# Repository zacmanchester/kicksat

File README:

kicksat
=======

## This repository is no longer being updated.
## All KickSat-related work is now hosted at [github.com/kicksat](https://github.com/kicksat)

# License

[Creative Commons Attribution-ShareAlike 4.0 International](https://creativecommons.org/licenses/by-sa/4.0/)

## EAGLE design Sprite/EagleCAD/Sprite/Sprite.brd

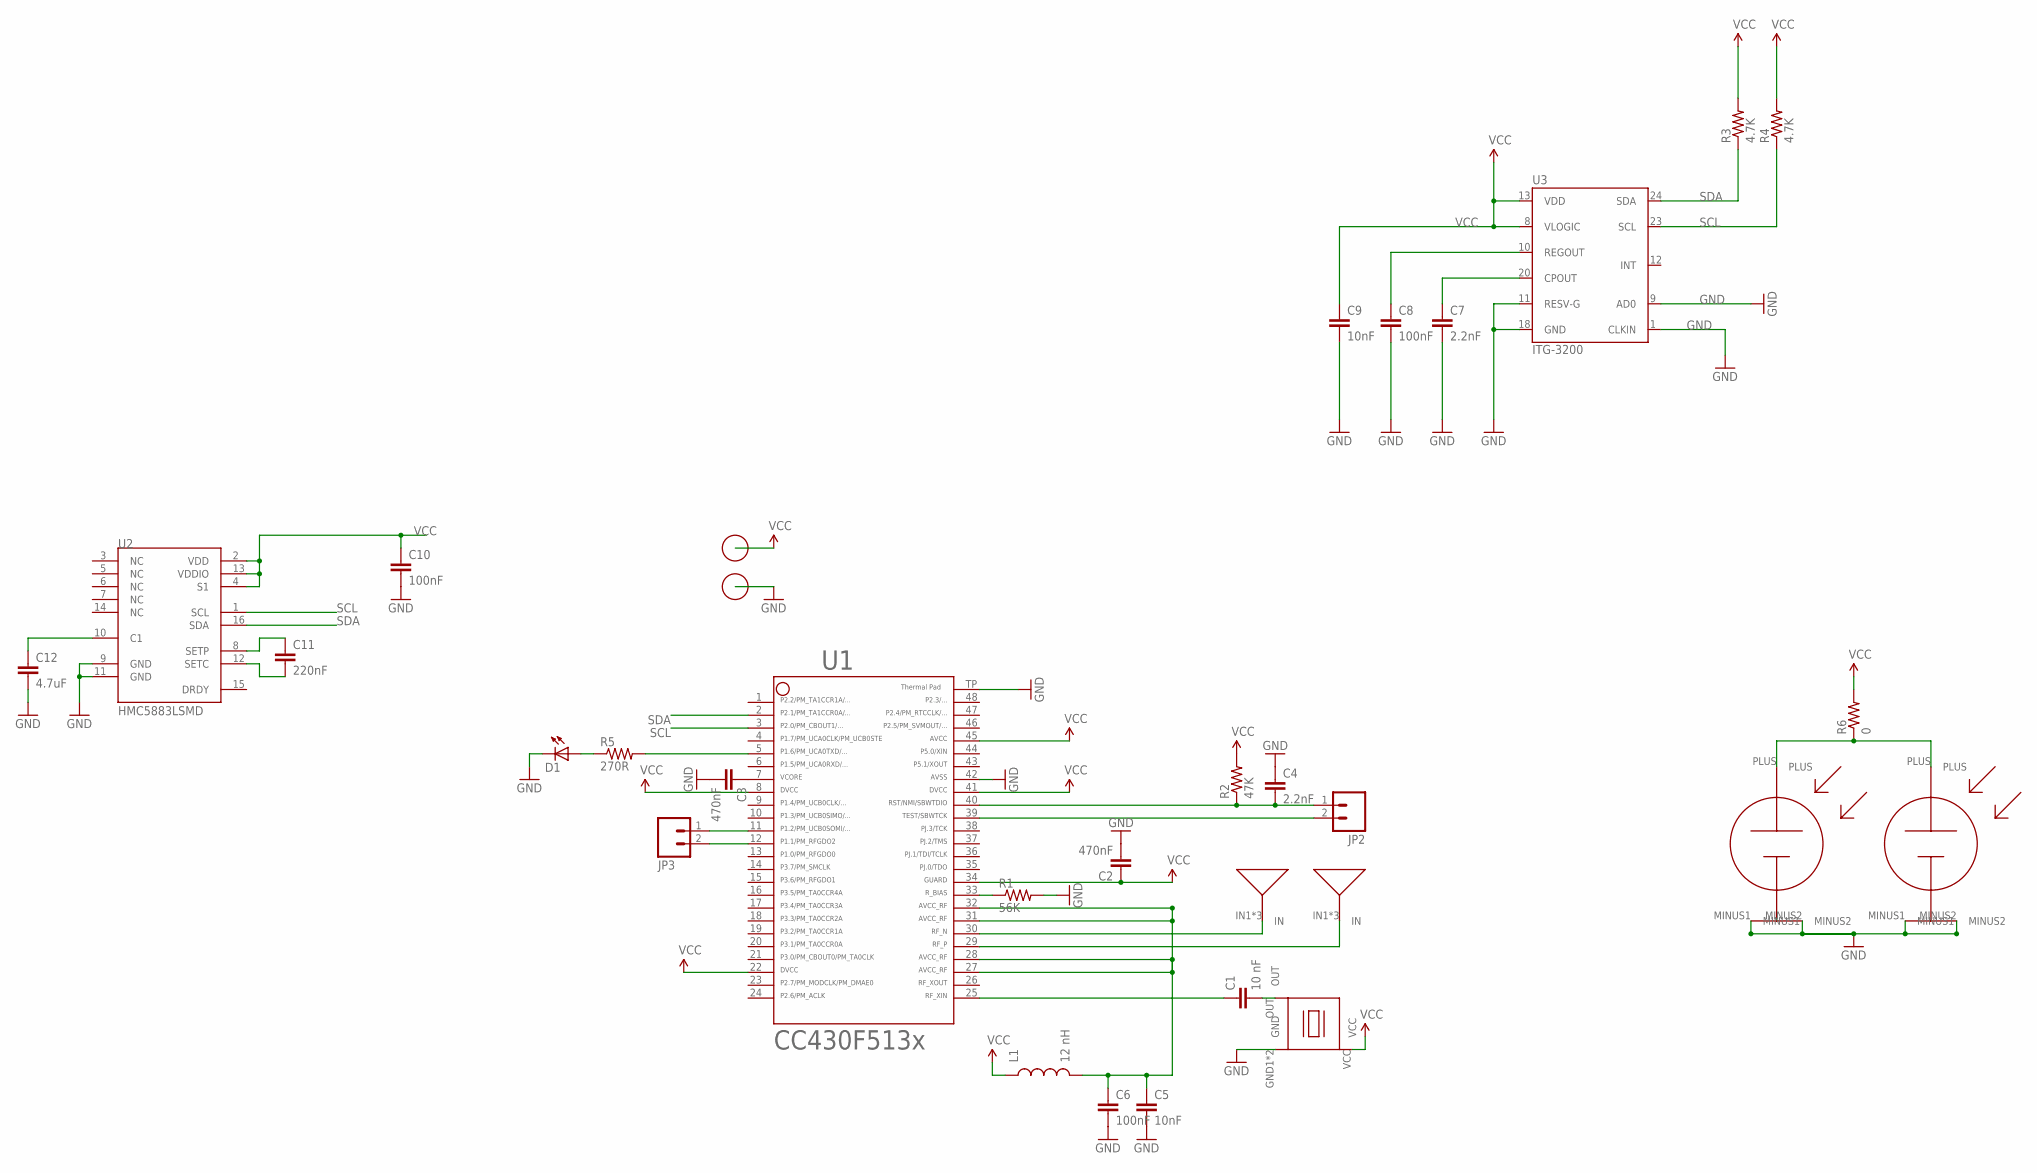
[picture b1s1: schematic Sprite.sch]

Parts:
ANT-N: ANTENNA
ANT-P: ANTENNA
C1: 10 nF; 0603-CAP
C2, C3: 470nF; 0603-CAP
C4, C7: 2.2nF; 0603-CAP
C5, C9: 10nF; 0603-CAP
C6, C8, C10: 100nF; 0603-CAP
C11: 220nF; 0603-CAP
C12: 4.7uF; 0603-CAP
D1: LED0603; LED-0603
JP2, JP3: M02PTH; 1X02
L1: 12 nH; 0603
P1, P2: SPRITE_PIN
R1: 56K; 0603-RES
R2: 47K; 0603-RES
R3, R4: 4.7K; 0603-RES
R5: 270R; 0603-RES
R6: 0; R0805
S1, S2: TASC
U1: CC430F5137; RGZ48
U2: HMC5883LSMD; 16LPCC
U3: ITG-3200; QFN-24
X1: TCXO_7Z; TXC_7Z

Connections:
GND: C2.2, C3.2, C4.1, C5.2, C6.2, C7.2, C8.2, C9.2, C10.2, C12.2, D1.C, R1.2, S1.MINUS1, S1.MINUS2, S2.MINUS1, S2.MINUS2, U1.42, U1.TP (49), U2.9 (GND), U2.11 (GND), U3.1 (CLKIN), U3.9 (AD0), U3.11 (RESV-G), U3.18 (GND), X1.GND1 (GND), X1.GND2 (GND)
unnamed: C1.1, U1.25
unnamed: R1.1, U1.33
unnamed: C3.1, U1.7
unnamed: C11.1, U2.8 (SETP)
unnamed: C11.2, U2.12 (SETC)
unnamed: C12.1, U2.10 (C1)
unnamed: C7.1, U3.20 (CPOUT)
unnamed: C8.1, U3.10 (REGOUT)
unnamed: R5.2, U1.5
unnamed: D1.A, R5.1
unnamed: C1.2, X1.OUT
RFN: ANT-N.IN1, ANT-N.IN2, ANT-N.IN3, U1.30
RFP: ANT-P.IN1, ANT-P.IN2, ANT-P.IN3, U1.29
RST: C4.2, JP2.1, R2.1, U1.40
RXD: JP3.2, U1.12
SCL: R4.1, U1.3, U2.1 (SCL), U3.23 (SCL)
SDA: R3.1, U1.2, U2.16 (SDA), U3.24 (SDA)
TEST: JP2.2, U1.39
TXD: JP3.1, U1.11
VCC: C2.1, C9.1, C10.1, L1.1, R2.2, R3.2, R4.2, R6.2, U1.8, U1.22, U1.34, U1.41, U1.45, U2.2 (VDD), U2.4 (S1), U2.13 (VDDIO), U3.8 (VLOGIC), U3.13 (VDD), X1.VCC
VCCRF: C5.1, C6.1, L1.2, U1.27, U1.28, U1.31, U1.32
VSOLAR: R6.1, S1.PLUS, S2.PLUS

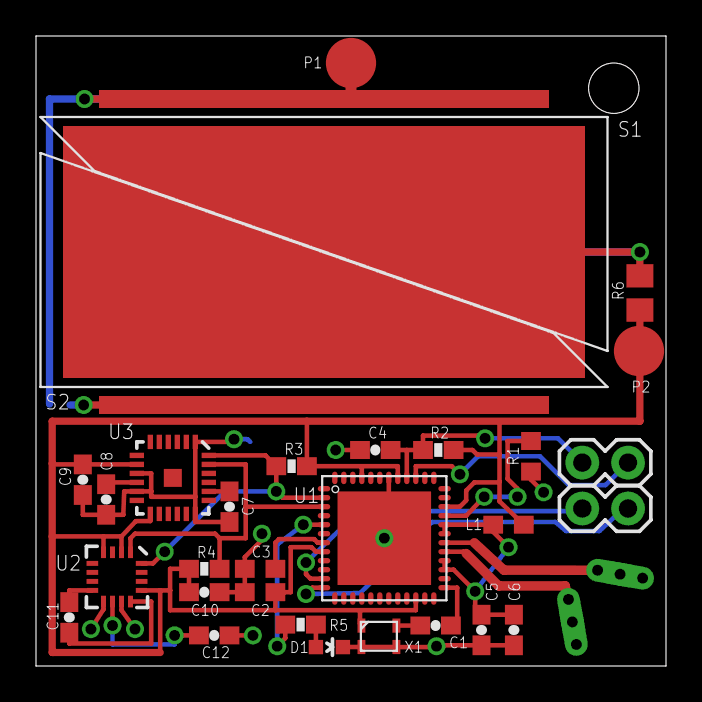
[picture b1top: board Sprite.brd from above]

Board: 2 copper layers, 35.0 x 35.0 mm, 32 parts (1 on the bottom side), 23 nets.

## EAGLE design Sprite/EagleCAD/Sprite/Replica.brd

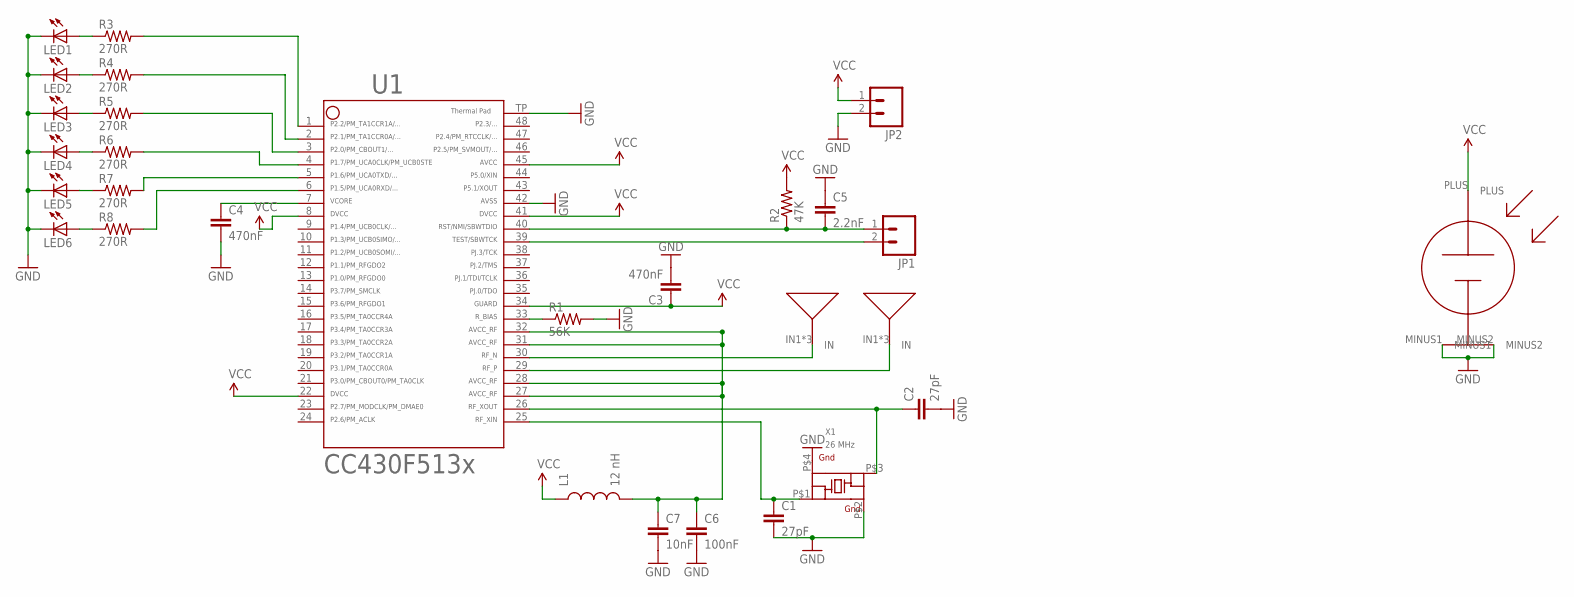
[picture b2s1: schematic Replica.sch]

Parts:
ANT-N: ANTENNA
ANT-P: ANTENNA
C1, C2: 27pF; 0603-CAP
C3, C4: 470nF; 0603-CAP
C5: 2.2nF; 0603-CAP
C6: 100nF; 0603-CAP
C7: 10nF; 0603-CAP
JP1, JP2: M02PTH; 1X02
L1: 12 nH; 0603
LED1, LED2, LED3, LED4, LED5, LED6: LED0603; LED-0603
R1: 56K; 0603-RES
R2: 47K; 0603-RES
R3, R4, R5, R6, R7, R8: 270R; 0603-RES
S1: TASC
U1: CC430F5137; RGZ48
X1: 26 MHz; ABM11_CERAMIC-SMD-CRYSTAL

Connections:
GND: C1.2, C2.2, C3.2, C4.2, C5.1, C6.2, C7.2, JP2.2, LED1.C, LED2.C, LED3.C, LED4.C, LED5.C, LED6.C, R1.2, S1.MINUS1, S1.MINUS2, U1.42, U1.TP (49), X1.P$2 (GROUND2), X1.P$4 (GROUND4)
unnamed: C2.1, U1.26, X1.P$3
unnamed: C1.1, U1.25, X1.P$1
unnamed: R1.1, U1.33
unnamed: R4.2, U1.2
unnamed: LED2.A, R4.1
unnamed: LED3.A, R5.1
unnamed: LED4.A, R6.1
unnamed: LED5.A, R7.1
unnamed: LED6.A, R8.1
unnamed: R3.2, U1.1
unnamed: LED1.A, R3.1
unnamed: R5.2, U1.3
unnamed: R6.2, U1.4
unnamed: R7.2, U1.5
unnamed: R8.2, U1.6
RFN: ANT-N.IN1, ANT-N.IN2, ANT-N.IN3, U1.30
RFP: ANT-P.IN1, ANT-P.IN2, ANT-P.IN3, U1.29
RST: C5.2, JP1.1, R2.1, U1.40
TEST: JP1.2, U1.39
VCC: C3.1, JP2.1, L1.1, R2.2, S1.PLUS, U1.8, U1.22, U1.34, U1.41, U1.45
VCCRF: C6.1, C7.1, L1.2, U1.27, U1.28, U1.31, U1.32
VCORE: C4.1, U1.7

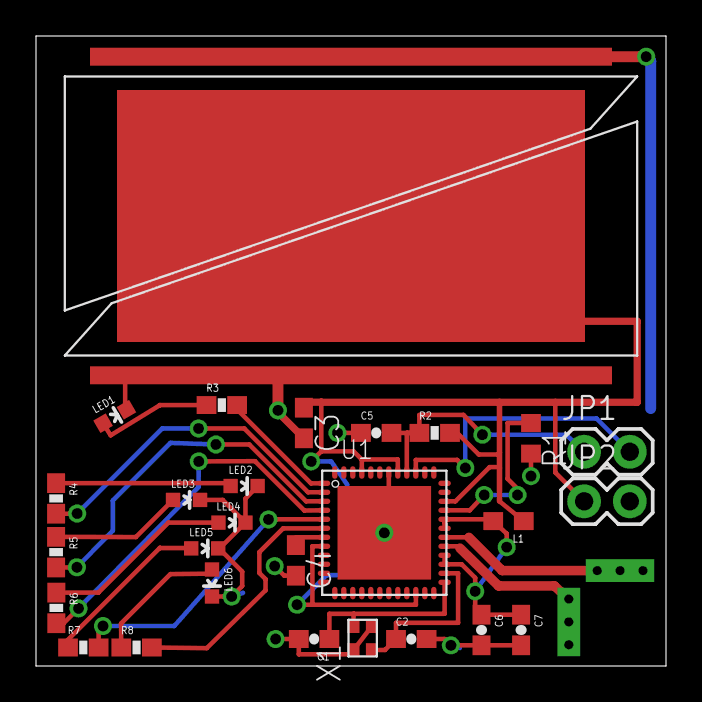
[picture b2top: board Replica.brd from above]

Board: 2 copper layers, 35.0 x 35.0 mm, 29 parts (0 on the bottom side), 23 nets.

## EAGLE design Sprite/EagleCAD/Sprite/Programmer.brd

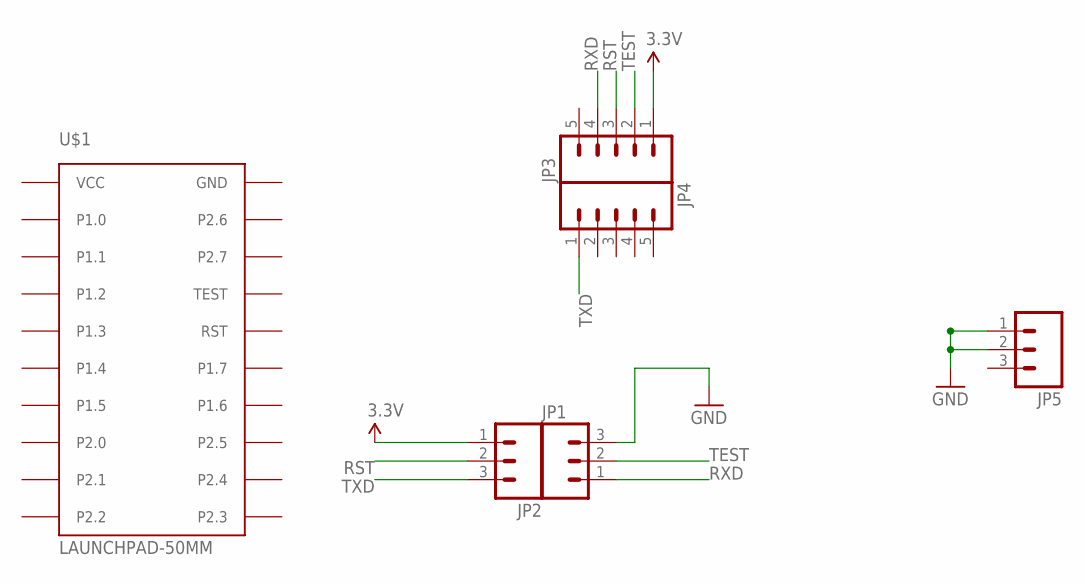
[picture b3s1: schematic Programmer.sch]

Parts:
JP1, JP2, JP5: M03LOCK; 1X03_LOCK
JP3, JP4: M05LOCK; 1X05_LOCK
U$1: LAUNCHPAD-50MM

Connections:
3.3V: JP2.1, JP3.1
GND: JP1.3, JP5.1, JP5.2, U$1.GND
RST: JP2.2, JP3.3
RXD: JP1.1, JP3.4
TEST: JP1.2, JP3.2
TXD: JP2.3, JP4.1
VCC: U$1.VCC

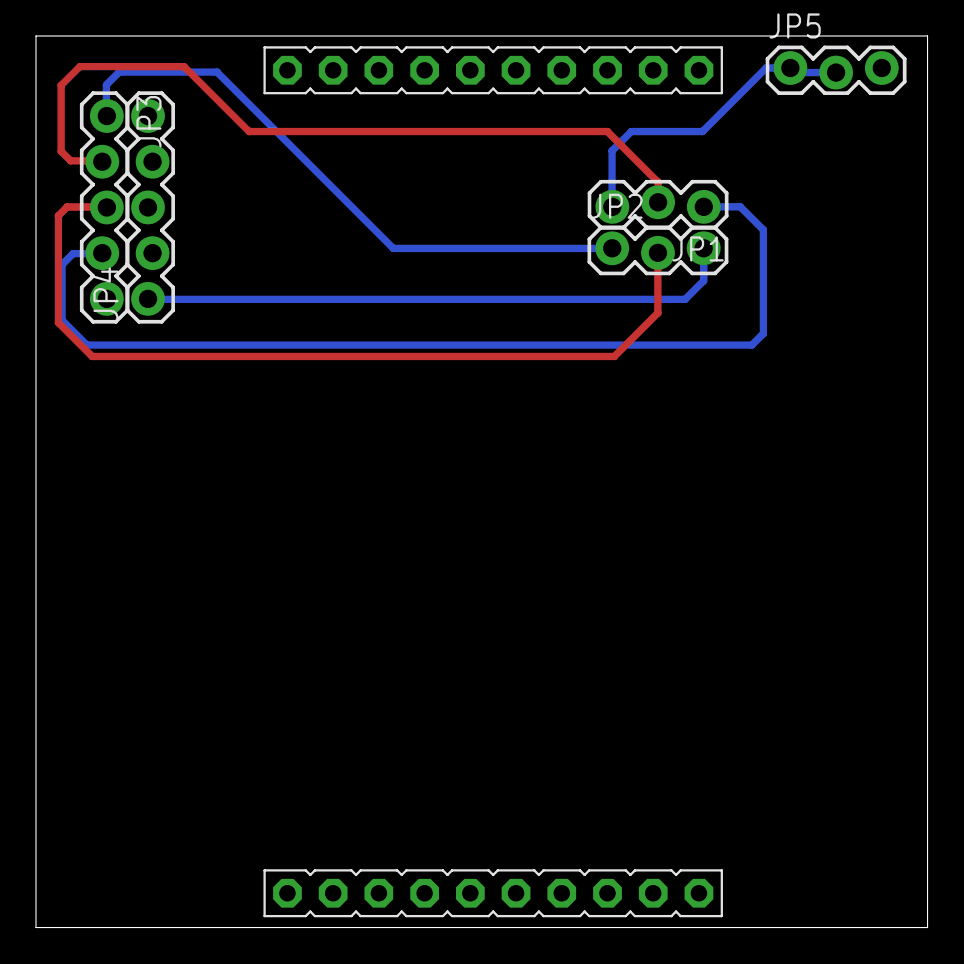
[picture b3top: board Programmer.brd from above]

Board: 2 copper layers, 49.5 x 49.5 mm, 6 parts (0 on the bottom side), 6 nets.

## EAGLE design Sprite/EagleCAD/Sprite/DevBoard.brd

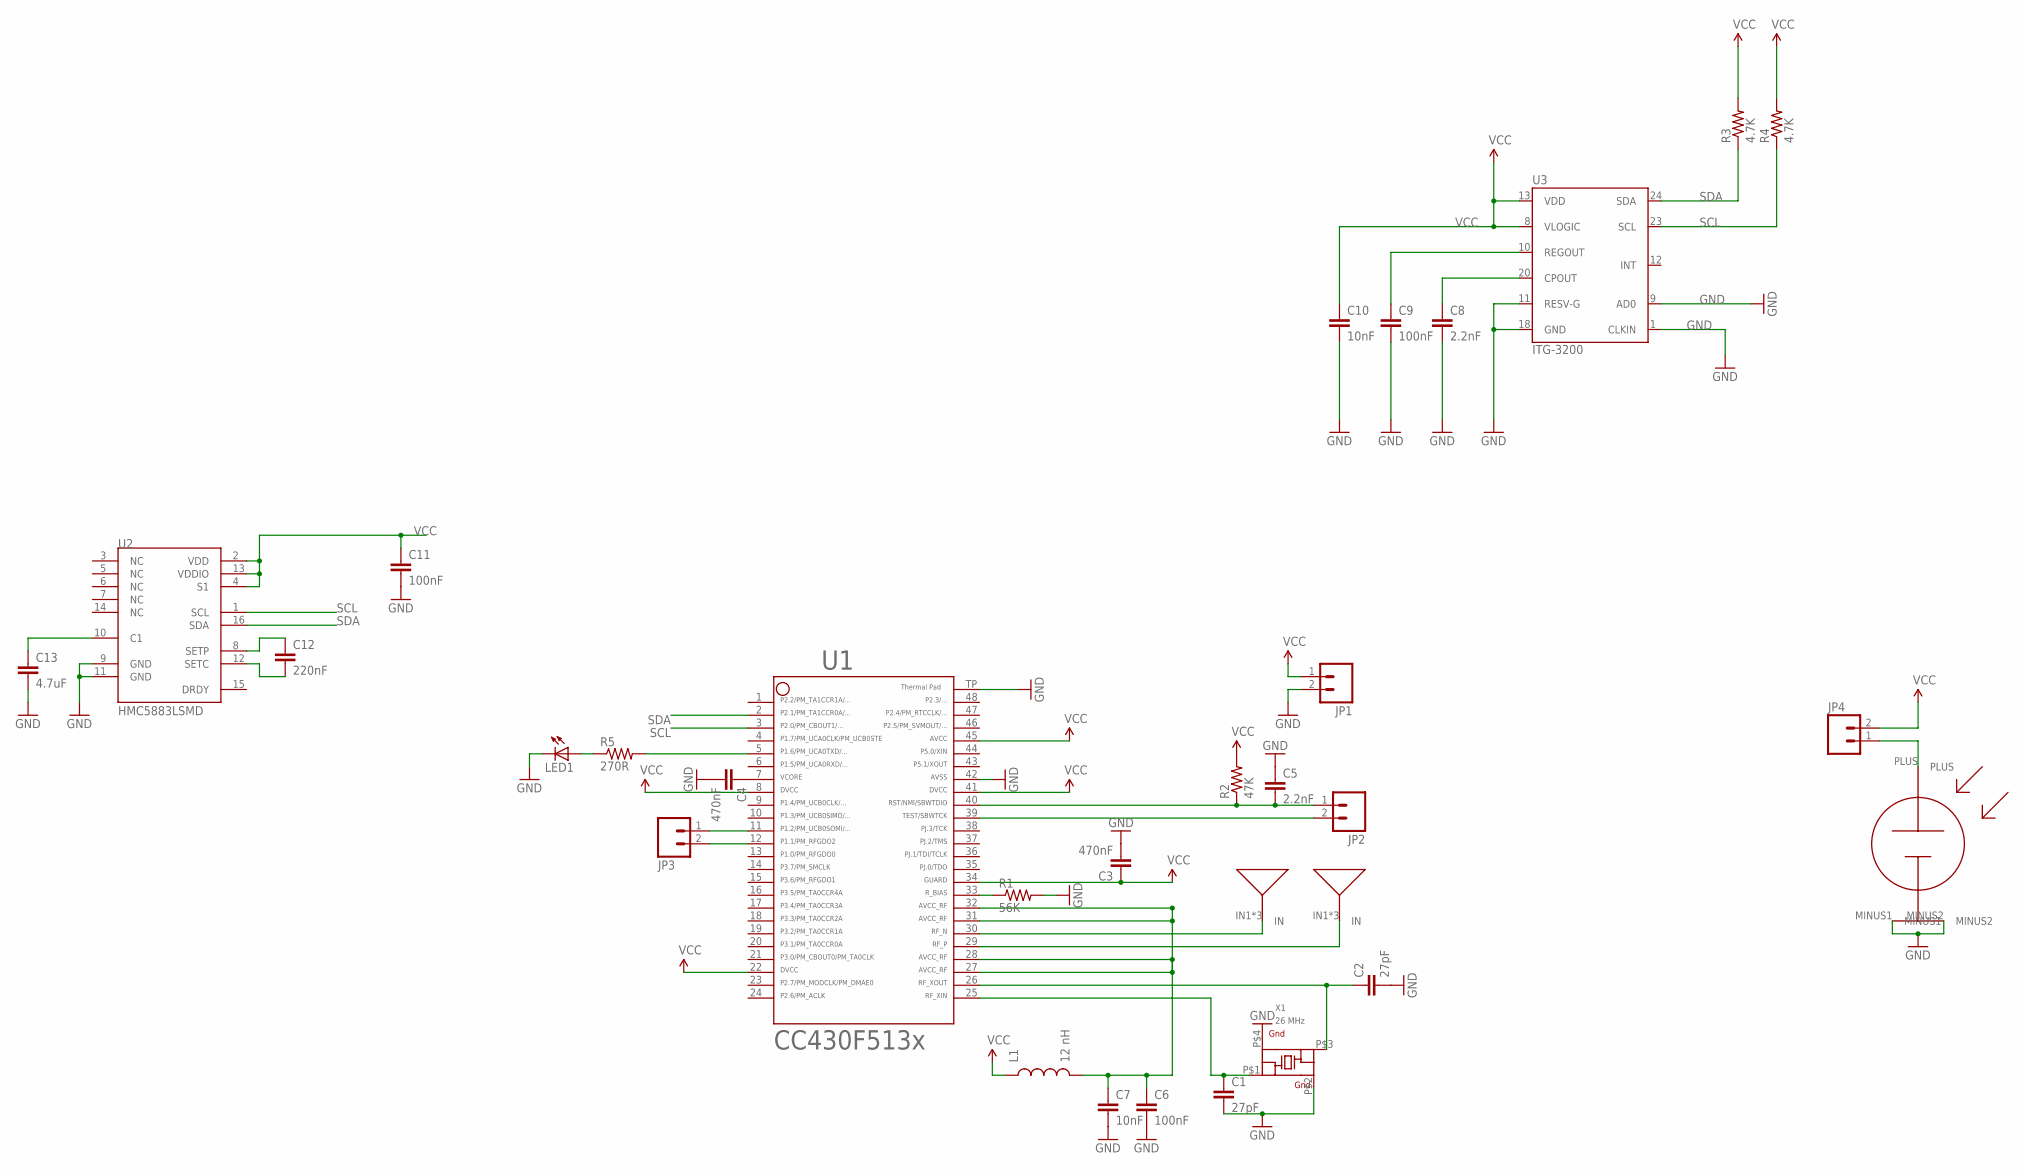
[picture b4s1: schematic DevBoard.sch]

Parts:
ANT-N: ANTENNA
ANT-P: ANTENNA
C1, C2: 27pF; 0603-CAP
C3, C4: 470nF; 0603-CAP
C5, C8: 2.2nF; 0603-CAP
C6, C9, C11: 100nF; 0603-CAP
C7, C10: 10nF; 0603-CAP
C12: 220nF; 0603-CAP
C13: 4.7uF; 0603-CAP
JP1, JP2, JP3, JP4: M02PTH; 1X02
L1: 12 nH; 0603
LED1: LED0603; LED-0603
R1: 56K; 0603-RES
R2: 47K; 0603-RES
R3, R4: 4.7K; 0603-RES
R5: 270R; 0603-RES
S1: TASC
U1: CC430F5137; RGZ48
U2: HMC5883LSMD; 16LPCC
U3: ITG-3200; QFN-24
X1: 26 MHz; ABM11_CERAMIC-SMD-CRYSTAL

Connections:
GND: C1.2, C2.2, C3.2, C4.2, C5.1, C6.2, C7.2, C8.2, C9.2, C10.2, C11.2, C13.2, JP1.2, LED1.C, R1.2, S1.MINUS1, S1.MINUS2, U1.42, U1.TP (49), U2.9 (GND), U2.11 (GND), U3.1 (CLKIN), U3.9 (AD0), U3.11 (RESV-G), U3.18 (GND), X1.P$2 (GROUND2), X1.P$4 (GROUND4)
unnamed: C2.1, U1.26, X1.P$3
unnamed: C1.1, U1.25, X1.P$1
unnamed: R1.1, U1.33
unnamed: C4.1, U1.7
unnamed: C12.1, U2.8 (SETP)
unnamed: C12.2, U2.12 (SETC)
unnamed: C13.1, U2.10 (C1)
unnamed: C8.1, U3.20 (CPOUT)
unnamed: C9.1, U3.10 (REGOUT)
unnamed: R5.2, U1.5
unnamed: LED1.A, R5.1
RFN: ANT-N.IN1, ANT-N.IN2, ANT-N.IN3, U1.30
RFP: ANT-P.IN1, ANT-P.IN2, ANT-P.IN3, U1.29
RST: C5.2, JP2.1, R2.1, U1.40
RX: JP3.1, U1.11
SCL: R4.1, U1.3, U2.1 (SCL), U3.23 (SCL)
SDA: R3.1, U1.2, U2.16 (SDA), U3.24 (SDA)
TEST: JP2.2, U1.39
TX: JP3.2, U1.12
VCC: C3.1, C10.1, C11.1, JP1.1, JP4.2, L1.1, R2.2, R3.2, R4.2, U1.8, U1.22, U1.34, U1.41, U1.45, U2.2 (VDD), U2.4 (S1), U2.13 (VDDIO), U3.8 (VLOGIC), U3.13 (VDD)
VCCRF: C6.1, C7.1, L1.2, U1.27, U1.28, U1.31, U1.32
VSOLAR: JP4.1, S1.PLUS

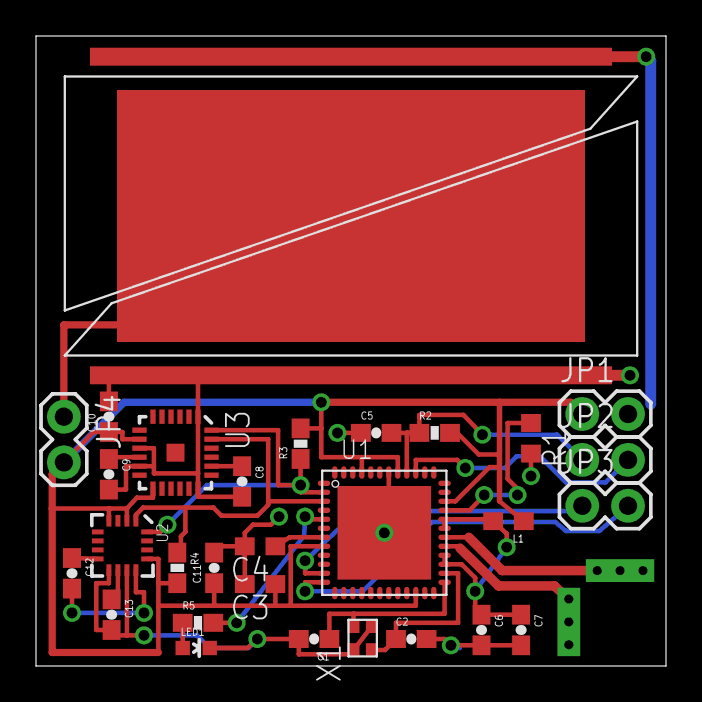
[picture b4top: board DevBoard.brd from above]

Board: 2 copper layers, 35.0 x 35.0 mm, 31 parts (0 on the bottom side), 23 nets.

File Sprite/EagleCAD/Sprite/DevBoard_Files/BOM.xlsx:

Part | Value | Device | Package
C1 | 27pF | CAP0603-CAP | 0603-CAP
C2 | 27pF | CAP0603-CAP | 0603-CAP
C3 | 470nF | CAP0603-CAP | 0603-CAP
C4 | 470nF | CAP0603-CAP | 0603-CAP
C5 | 2.2nF | CAP0603-CAP | 0603-CAP
C6 | 100nF | CAP0603-CAP | 0603-CAP
C7 | 10nF | CAP0603-CAP | 0603-CAP
C8 | 2.2nF | CAP0603-CAP | 0603-CAP
C9 | 100nF | CAP0603-CAP | 0603-CAP
C10 | 10nF | CAP0603-CAP | 0603-CAP
C11 | 100nF | CAP0603-CAP | 0603-CAP
C12 | 220nF | CAP0603-CAP | 0603-CAP
C13 | 4.7uF | CAP0603-CAP | 0603-CAP
JP1 | DNP | DNP | DNP
JP2 | DNP | DNP | DNP
JP3 | DNP | DNP | DNP
JP4 | DNP | DNP | DNP
L1 | 12nH | INDUCTOR | 0603-INDUCTOR
LED1 | LED0603 | LED-0603 | 0603-LED
R1 | 56K | RESISTOR0603-RES | 0603-RES
R2 | 47K | RESISTOR0603-RES | 0603-RES
R3 | 4.7K | RESISTOR0603-RES | 0603-RES
R4 | 4.7K | RESISTOR0603-RES | 0603-RES
R5 | 270R | RESISTOR0603-RES | 0603-RES
R6 | 0R | RESISTOR0805-RES | 0805-RES
R7 | 0R | RESISTOR0805-RES | 0805-RES
S1 | TASC | TASC | TASC
S2` | TASC | TASC | TASC
U1 | CC430F5137 | CC430F513X---RGZ48 | QFN-48
U2 | HMC5883LSMD | HMC5883LSMD | 16-LPCC
U3 | ITG-3200 | ITG-3200 | QFN-24
X1 | 26MHz | ABM11-XTAL | ABM11_CERAMIC_SMD_CRYSTALABM11

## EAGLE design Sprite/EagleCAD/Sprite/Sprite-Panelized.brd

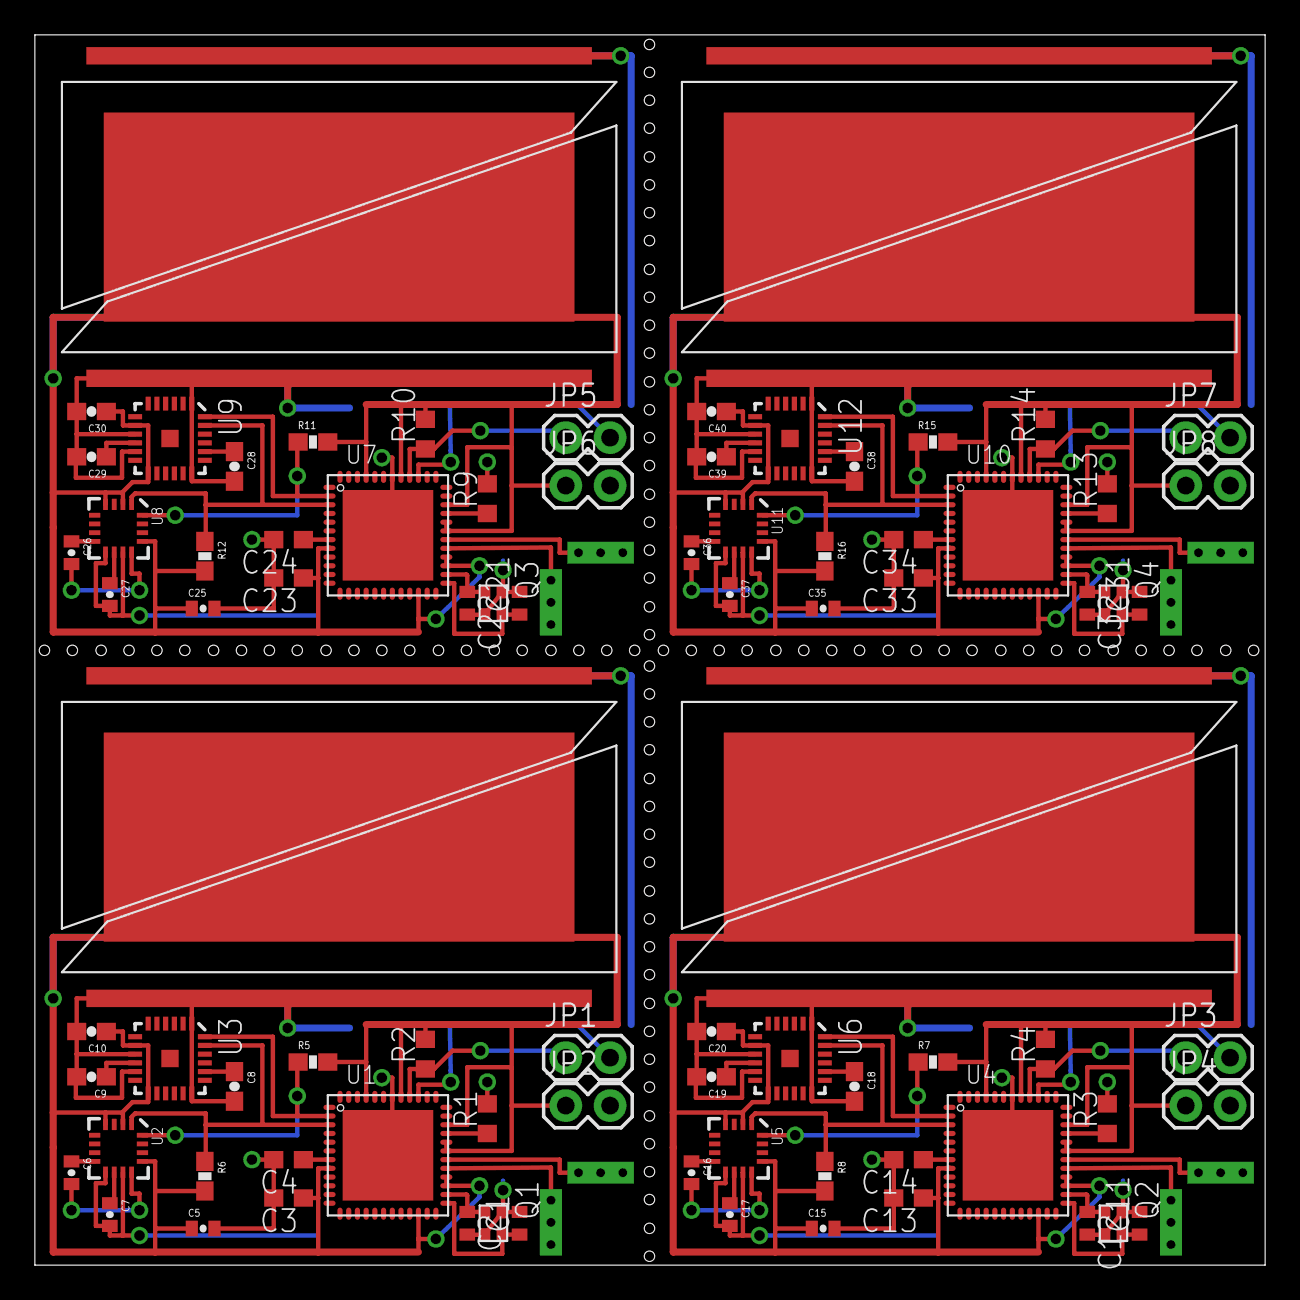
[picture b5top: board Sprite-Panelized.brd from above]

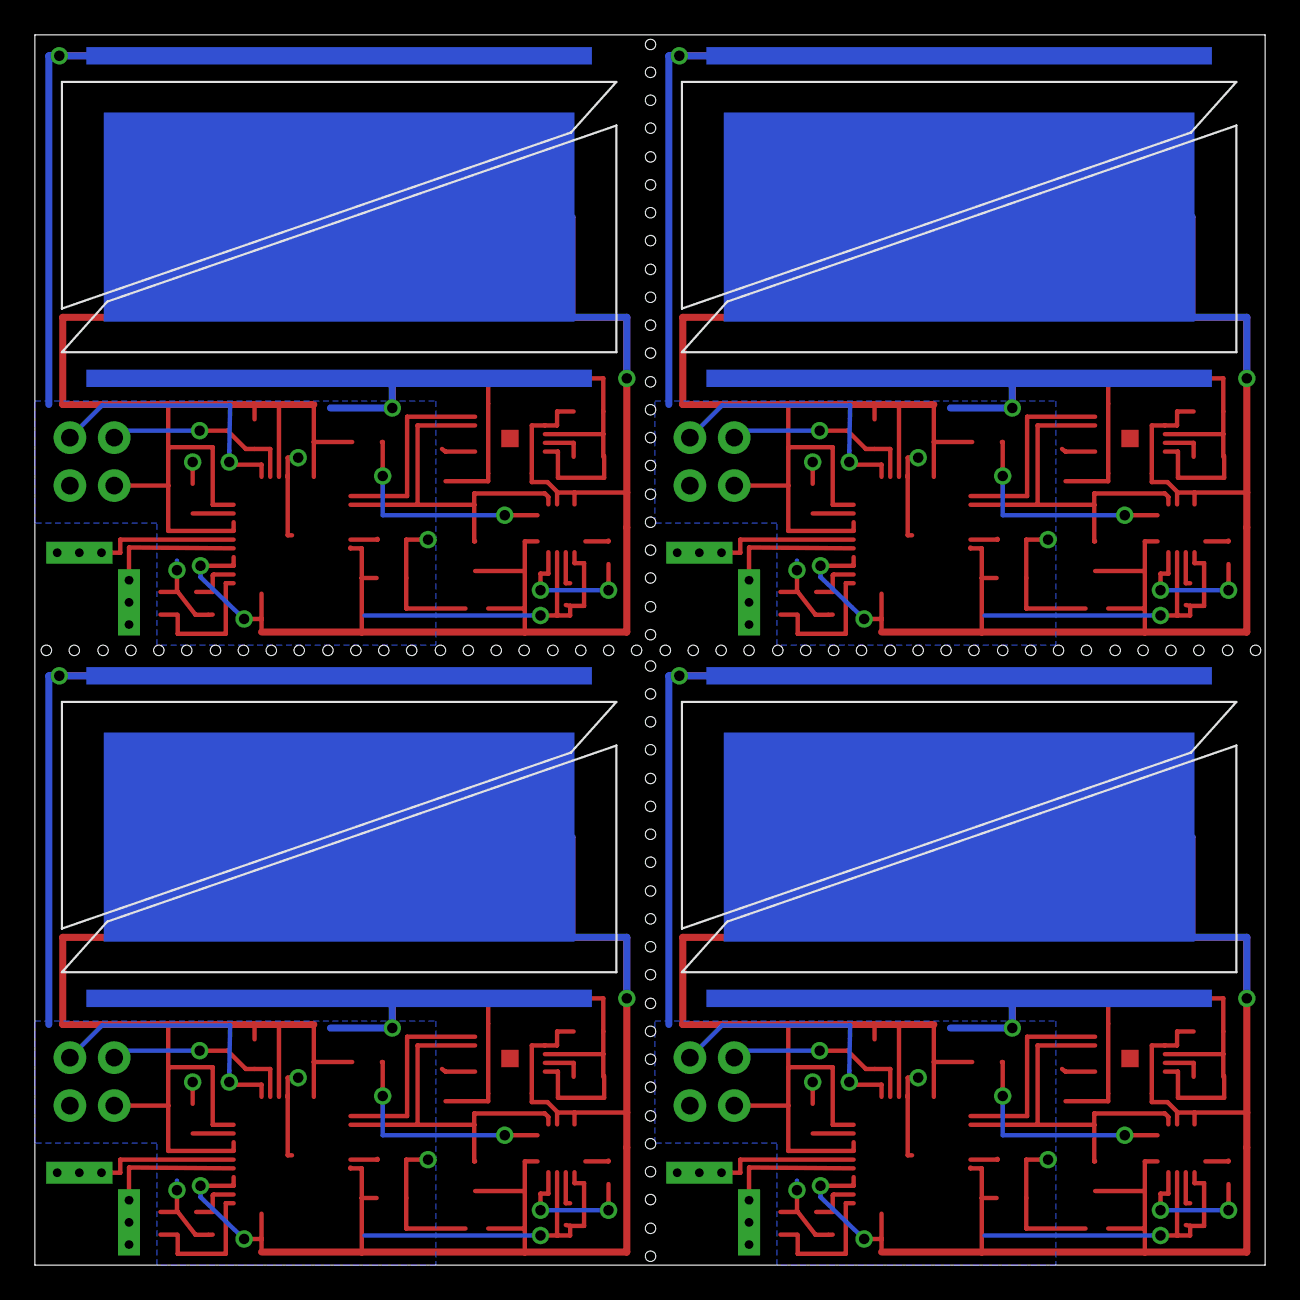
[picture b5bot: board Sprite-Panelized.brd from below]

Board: 2 copper layers, 70.6 x 70.6 mm, 96 parts (4 on the bottom side), 68 nets.

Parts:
C1, C2, C11, C12, C21, C22, C31, C32: 27 pF; C0402
C3, C4, C13, C14, C23, C24, C33, C34: 470 nF; C0603
C5, C15, C25, C35: .1uF; 0402-CAP
C6, C16, C26, C36: .22uF; 0402-CAP
C7, C17, C27, C37: 4.7uF; 0402-CAP
C8, C18, C28, C38: 2.2nF; 0603-CAP
C9, C19, C29, C39: 0.1uF; 0603-CAP
C10, C20, C30, C40: 10nF; 0603-CAP
JP1, JP2, JP3, JP4, JP5, JP6, JP7, JP8: 1X02
Q1, Q2, Q3, Q4: ABM11; ABM11_CERAMIC-SMD-CRYSTAL
R1, R3, R9, R13: 56 K; R0603
R2, R4, R10, R14: 47 K; R0603
R5, R6, R7, R8, R11, R12, R15, R16: DNP; 0603-RES
S1, S2, S3, S4, S5, S6, S7, S8: TASC
U1, U4, U7, U10: CC430F5137; RGZ48
U2, U5, U8, U11: HMC5883LSMD; 16LPCC
U3, U6, U9, U12: ITG-3200; QFN-24
U$1, U$2, U$3, U$4, U$5, U$6, U$7, U$8: ANTENNA

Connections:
GND: C1.2, C2.2, C3.2, C4.2, C5.2, C7.2, C8.2, C9.2, C10.2, JP2.2, Q1.P$2, Q1.P$4, R1.2, S1.MINUS1, S1.MINUS2, S2.MINUS1, S2.MINUS2, U1.42, U1.TP, U2.9, U2.11, U3.1, U3.9, U3.11, U3.18
GND1: C11.2, C12.2, C13.2, C14.2, C15.2, C17.2, C18.2, C19.2, C20.2, JP4.2, Q2.P$2, Q2.P$4, R3.2, S3.MINUS1, S3.MINUS2, S4.MINUS1, S4.MINUS2, U4.42, U4.TP, U5.9, U5.11, U6.1, U6.9, U6.11, U6.18
GND2: C21.2, C22.2, C23.2, C24.2, C25.2, C27.2, C28.2, C29.2, C30.2, JP6.2, Q3.P$2, Q3.P$4, R9.2, S5.MINUS1, S5.MINUS2, S6.MINUS1, S6.MINUS2, U7.42, U7.TP, U8.9, U8.11, U9.1, U9.9, U9.11, U9.18
GND3: C31.2, C32.2, C33.2, C34.2, C35.2, C37.2, C38.2, C39.2, C40.2, JP8.2, Q4.P$2, Q4.P$4, R13.2, S7.MINUS1, S7.MINUS2, S8.MINUS1, S8.MINUS2, U10.42, U10.TP, U11.9, U11.11, U12.1, U12.9, U12.11, U12.18
unnamed: C2.1, Q1.P$3, U1.26
unnamed: C1.1, Q1.P$1, U1.25
unnamed: R1.1, U1.33
unnamed: C4.1, U1.7
unnamed: C6.1, U2.8
unnamed: C6.2, U2.12
unnamed: C7.1, U2.10
unnamed: C8.1, U3.20
unnamed: C9.1, U3.10
unnamed: C12.1, Q2.P$3, U4.26
unnamed: C11.1, Q2.P$1, U4.25
unnamed: R3.1, U4.33
unnamed: C14.1, U4.7
unnamed: C16.1, U5.8
unnamed: C16.2, U5.12
unnamed: C17.1, U5.10
unnamed: C18.1, U6.20
unnamed: C19.1, U6.10
unnamed: C22.1, Q3.P$3, U7.26
unnamed: C21.1, Q3.P$1, U7.25
unnamed: R9.1, U7.33
unnamed: C24.1, U7.7
unnamed: C26.1, U8.8
unnamed: C26.2, U8.12
unnamed: C27.1, U8.10
unnamed: C28.1, U9.20
unnamed: C29.1, U9.10
unnamed: C32.1, Q4.P$3, U10.26
unnamed: C31.1, Q4.P$1, U10.25
unnamed: R13.1, U10.33
unnamed: C34.1, U10.7
unnamed: C36.1, U11.8
unnamed: C36.2, U11.12
unnamed: C37.1, U11.10
unnamed: C38.1, U12.20
unnamed: C39.1, U12.10
RFN: U1.30, U$1.IN1, U$1.IN2, U$1.IN3
RFN1: U4.30, U$3.IN1, U$3.IN2, U$3.IN3
RFN2: U7.30, U$5.IN1, U$5.IN2, U$5.IN3
RFN3: U10.30, U$7.IN1, U$7.IN2, U$7.IN3
RFP: U1.29, U$2.IN1, U$2.IN2, U$2.IN3
RFP1: U4.29, U$4.IN1, U$4.IN2, U$4.IN3
RFP2: U7.29, U$6.IN1, U$6.IN2, U$6.IN3
RFP3: U10.29, U$8.IN1, U$8.IN2, U$8.IN3
RST: JP1.1, R2.1, U1.40
RST1: JP3.1, R4.1, U4.40
RST2: JP5.1, R10.1, U7.40
RST3: JP7.1, R14.1, U10.40
SCL: R6.1, U1.3, U2.1, U3.23
SCL1: R8.1, U4.3, U5.1, U6.23
SCL2: R12.1, U7.3, U8.1, U9.23
SCL3: R16.1, U10.3, U11.1, U12.23
SDA: R5.1, U1.2, U2.16, U3.24
SDA1: R7.1, U4.2, U5.16, U6.24
SDA2: R11.1, U7.2, U8.16, U9.24
SDA3: R15.1, U10.2, U11.16, U12.24
TEST: JP1.2, U1.39
TEST1: JP3.2, U4.39
TEST2: JP5.2, U7.39
TEST3: JP7.2, U10.39
VCC: C3.1, C5.1, C10.1, JP2.1, R2.2, R5.2, R6.2, S1.PLUS, S2.PLUS, U1.8, U1.22, U1.27, U1.28, U1.31, U1.32, U1.34, U1.41, U1.45, U2.2, U2.4, U2.13, U3.8, U3.13
VCC1: C13.1, C15.1, C20.1, JP4.1, R4.2, R7.2, R8.2, S3.PLUS, S4.PLUS, U4.8, U4.22, U4.27, U4.28, U4.31, U4.32, U4.34, U4.41, U4.45, U5.2, U5.4, U5.13, U6.8, U6.13
VCC2: C23.1, C25.1, C30.1, JP6.1, R10.2, R11.2, R12.2, S5.PLUS, S6.PLUS, U7.8, U7.22, U7.27, U7.28, U7.31, U7.32, U7.34, U7.41, U7.45, U8.2, U8.4, U8.13, U9.8, U9.13
VCC3: C33.1, C35.1, C40.1, JP8.1, R14.2, R15.2, R16.2, S7.PLUS, S8.PLUS, U10.8, U10.22, U10.27, U10.28, U10.31, U10.32, U10.34, U10.41, U10.45, U11.2, U11.4, U11.13, U12.8, U12.13

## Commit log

2012-03-01 edited ignored file types
2012-03-01 Added Link Budget Spreadsheet
2012-03-13 Created gh-pages branch via GitHub
2012-03-14 Moved stuff to KickSat-Internal
2012-03-14 Revert "Merge branch 'gh-pages'"
    This reverts commit b40f65a02fbc4b3aaa6879afae2e85818bb3bf31, reversing
    changes made to b43827cdeee5b81235b853cba69fb85e95e59801.
2012-03-14 First pages commit:
2012-03-14 Revert "First pages commit:"
    This reverts commit 2d9a53e0e1d64613a91a14a17899012b83274675.
2012-05-21 New webpage
2012-05-21 Added gitignore
2012-05-21 Updated gitignore
2012-05-21 Initial upload
2012-05-22 Fixed typo
2012-06-13 Removed R2 and changed all passives to 0605 packages
    Removed pull-up resistor on RST line of CC430 (R2)
2012-06-13 Moved GND strip closer to TASC cells + removed bottom cells
2012-06-13 Revert "Removed R2 and changed all passives to 0605 packages"
    This reverts commit fe0fb0a19ac4f8aff1bc8119a0abeef84ddcba56.
2012-06-13 Revert "Moved GND strip closer to TASC cells + removed bottom cells"
    This reverts commit a51b0ba4fb3e3dccbe7975012f3db8ac667cb900.
2012-06-13 Revert "Revert "Removed R2 and changed all passives to 0605 packages""
    This reverts commit b3ebe1b95578add26a06b9776380b87bb7788d05.
2012-06-13 Revert "Revert "Moved GND strip closer to TASC cells + removed bottom cells""
    This reverts commit 1dc39e584056e569c73cdb2ce6a50d93971a399e.
2012-06-13 Removed old panelized board, fixed all pullups
2012-06-19 Link budget edits
2012-06-19 Added board Gerber files
2012-06-21 Sprite AVCC_RF Decoupling
    Added decoupling caps and inductor to AVCC_RF to decouple from DVCC
2012-06-22 Updated Gerbers + small tweaks
2012-06-23 Changed antenna feed line traces to 50 ohm microstrips
    Calculated assuming 31 mil board thickness
2012-06-23 Updated Gerbers
2012-07-10 XTAL and Solar Cell fixes
    Fixed alignment of crystal and moved ground pads on TASC cells further
    apart
2012-07-10 Deleted Gerbers.zip
2012-07-11 Added LED for debugging purposes, fixed crystal layout
2012-07-11 Some cleanup, updated BOM
2012-07-11 Added replica board
    Replica board has sensors removed and cool silkscreen + LEDs instead
2012-07-11 Replica board - put each LED on it's own pin
2012-07-11 Tweaked replica board for Sunstone design rules
2012-07-23 Added header to dev board to disconnect solar cells
    Added a header to connect/disconnect the solar cells from VCC to allow
    programming with the TI launchpad
2012-08-09 Checked souvenir for seeed studio design rules
2012-08-17 Stuff for Seeed Propagate
2012-08-17 Tweaks to text
2012-08-31 Added headers for serial port
    Put an extra pair of headers on the board to interface with a serial
    port for Energia debugging. Still have to figure out which MCU pins to
    use
2012-09-04 Beginnings of GNURadio signal processing code
2012-09-13 Receiver work
2012-09-13 Receiver fixes
    Fixes to get swig working. Compiles… testing needed
2012-09-14 FFT based receiver implementation
2012-09-15 More receiver work
2012-09-16 Working beacon receiver
    Stopped using Eigne library - strange threading issues. The correlator
    block now reliably detects a Sprite beacon signal
2012-09-17 Updated link budget
2012-09-17 More link budget tweaks
2012-09-18 Removed unnecessary file
2012-09-19 Added link budget for KickSat bus
2012-09-19 Link budget tweaks
2012-09-20 Sprite programmer sheild for launchpad
2012-09-20 Connected serial pins on dev board
2012-10-03 Programmer Board
    Finished programmer shield board
2012-10-04 Finished Programmer Board
    Added KickSat Silkscreen
2012-10-12 Fixed some issues on programmer
    GND trace wasn't connected to pin
2012-10-25 Replica files as ordered, GNURadio blocks
2012-10-25 Fixed BOM
2012-11-05 Small tweaks to correlator
    Converted to complex input -> float output
2012-11-12 DevBoard Gerbers
2012-11-12 Picture showing 0 ohm resistors
2012-11-13 Gerbers for programmer boards
2012-11-13 Folder rename
2012-11-15 Updated DevBoard BOM with Digikey Part Numbers
2012-11-20 Added mfg. Part numbers to BOM
2012-12-02 BOM Update
2012-12-07 Adding bit detector
2012-12-07 Work on bit detector
2012-12-07 Addid Std. Deviation Block
2012-12-07 Work on std. dev. block
2012-12-09 Std. Dev. Block Compiling
2012-12-14 Lengthened std. deviation window to 5120 samples
2012-12-14 Added bit threshold block. Not working yet.
2012-12-17 Bit threshold block working
2012-12-17 Changed bit threshold logic - should be more robust
2012-12-18 Tweaked std. dev. implementation - should be more efficient
2013-01-05 Added Energia example code
2013-01-05 Fixed an Energia demo for newer radio library
2013-01-08 Changed frequencies to 437.24 MHz
2013-01-09 Fixed bug in correlator
2013-01-09 Fixed a bug in bit thresholder
2013-01-09 Changed Energia test code
2013-01-09 Added Bit Decimator block to receiver
2013-01-22 Cleanup of demos for dev kits
2013-01-25 Added wiki and blog links to top of page
2013-01-25 Changed paragraph order
2013-01-28 Cleanup of example code
2013-01-29 Cleanup of GNURadio Files
2013-01-31 Initial work on decoder
2013-01-31 Tweaked RadioData demo
2013-01-31 Partially working decoder
2013-02-06 small tweaks to decoder
2013-02-08 Changed RadioData example to use Hamming encoder
2013-02-08 Added soft bit decimator
2013-02-08 Begining of soft decoder
2013-02-08 Added codeword matrix to soft decoder
2013-02-08 Soft decoder working
2013-02-13 Adding compass demo
2013-02-13 Added compass demo
2013-02-14 Finished CompassDemo
    Writes compass heading to serial port and transmits over radio
2013-02-14 Tweaks to CompassDemo
2013-02-15 Added include for iostream library
2013-02-21 Added debug info output to decoder
2013-02-21 Demos with different PRNs
2013-02-21 Added expurgated (15,10,4) code to decoder
2013-02-22 changes to decoder
2013-02-25 New decoder implementation
2013-02-26 Changed decoder to use (16,8,5) block code
2013-02-26 Changed test code
2013-02-26 Fixes to new decoder code
2013-02-26 Changed to (12,8,3) block code with alignment preamble
2013-02-27 Decoder improvements
2013-03-07 Changed to (16,8,5) block code with 4 bit preamble
2013-03-07 Added postamble
2013-03-12 Decoder fully working
2013-03-26 Changed receiver to 640 bit SLCE Codes
2013-03-27 Set up Sprite for SLCE Codes
2013-03-27 Receiver working with SLCE Codes
2013-04-02 Added file sink/source blocks
2013-04-03 Added back solar cells and TCXO to Sprite
2013-04-24 New Sprite design
    Several tweaks to the Sprite on the way to the flight unit. Added pins
    and holes to interface to the deployer as well as a TCXO.
2013-05-11 Tightened up spacing between tasc cells and ground pads
2013-05-17 Adding radio install script for Ubuntu
2013-05-17 Fixes to install script
2013-05-31 Made corner hole 2.8 mm
2013-06-24 Updated Gerbers and BOM for new Sprite order
2013-06-26 Fixed silksreen on Sprite board
2013-06-26 Updated Gerbers for Sprite
2013-07-06 Updated install of RTL-SDR GNURadio Block to checkout 3.6 branch now that gr-osmosdr trunk has moved to 3.7.
2013-07-10 Silkscreen + BOM fixes, added paste layers to gerbers
2013-07-16 Added DRUs
2013-07-16 Updated images
2013-07-22 Added Sunstone CAM jobs
2013-07-22 Edits to 6-layer CAM job
2013-07-27 Added dev kit stickers
2013-09-16 Solar panel test data
2013-11-02 Moved all ground station stuff to kicksat-groundstation repository
2013-11-02 Edited .gitignore
2013-11-19 Fixed frequency in comments
2013-11-23 Switched to 511 bit Gold codes
2013-11-24 Added kickstarter badge
2013-11-26 Added video
2014-01-27 Added finished pictures of laser engravings
2014-01-27 Changed name of folder
2014-01-27 Added -X zoomed in photos
2014-01-27 Swapped out -X4
2014-01-27 Added -Y zoomed-in photos
2014-01-27 Added +X zoomed-in photos
2014-01-27 Added +Y zoomed-in pictures
2014-01-30 Uploading new +X mid left photo
2014-01-30 Changing file extension...
2014-02-19 Added favicon
2014-02-19 Merging node and gh-pages index.html files
2014-03-11 Added ground station info link
2014-03-14 Website tweak
2014-04-08 Radio page with JotForm upload
2014-04-24 Added live tracker map
2014-04-24 Type
2014-05-14 Revert ec73028..c4ccd13
    This rolls back to commit ec73028f61fea69fea0d820cf8923a75d6711b73.
2014-06-02 Added OSH Park DRU

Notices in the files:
parts and their libraries:
SparkFun: Licensing: CC v3.0 Share-Alike You are welcome to use this library for commercial purposes.
